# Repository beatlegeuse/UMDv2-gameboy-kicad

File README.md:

# UMDv2-gameboy-kicad
UMDv2 Gameboy Cartridge Adapter

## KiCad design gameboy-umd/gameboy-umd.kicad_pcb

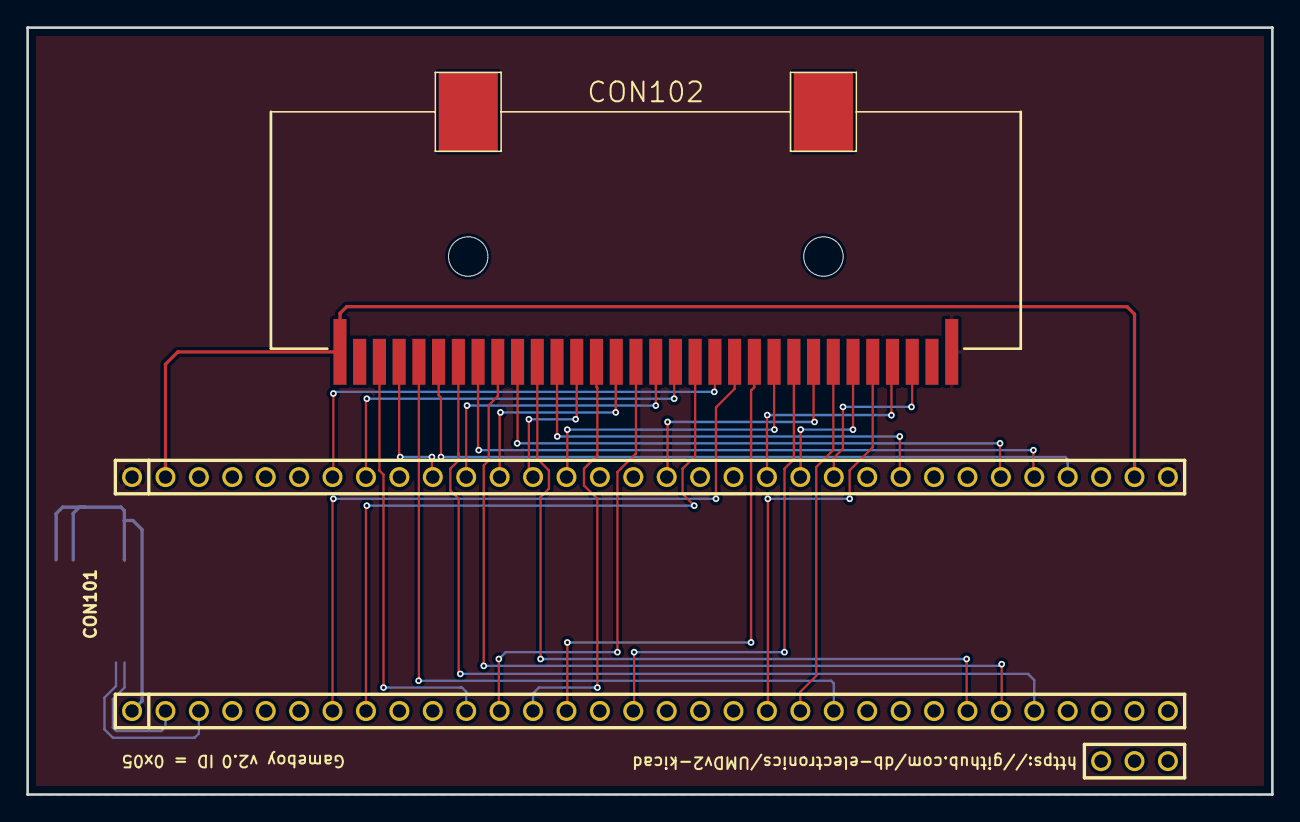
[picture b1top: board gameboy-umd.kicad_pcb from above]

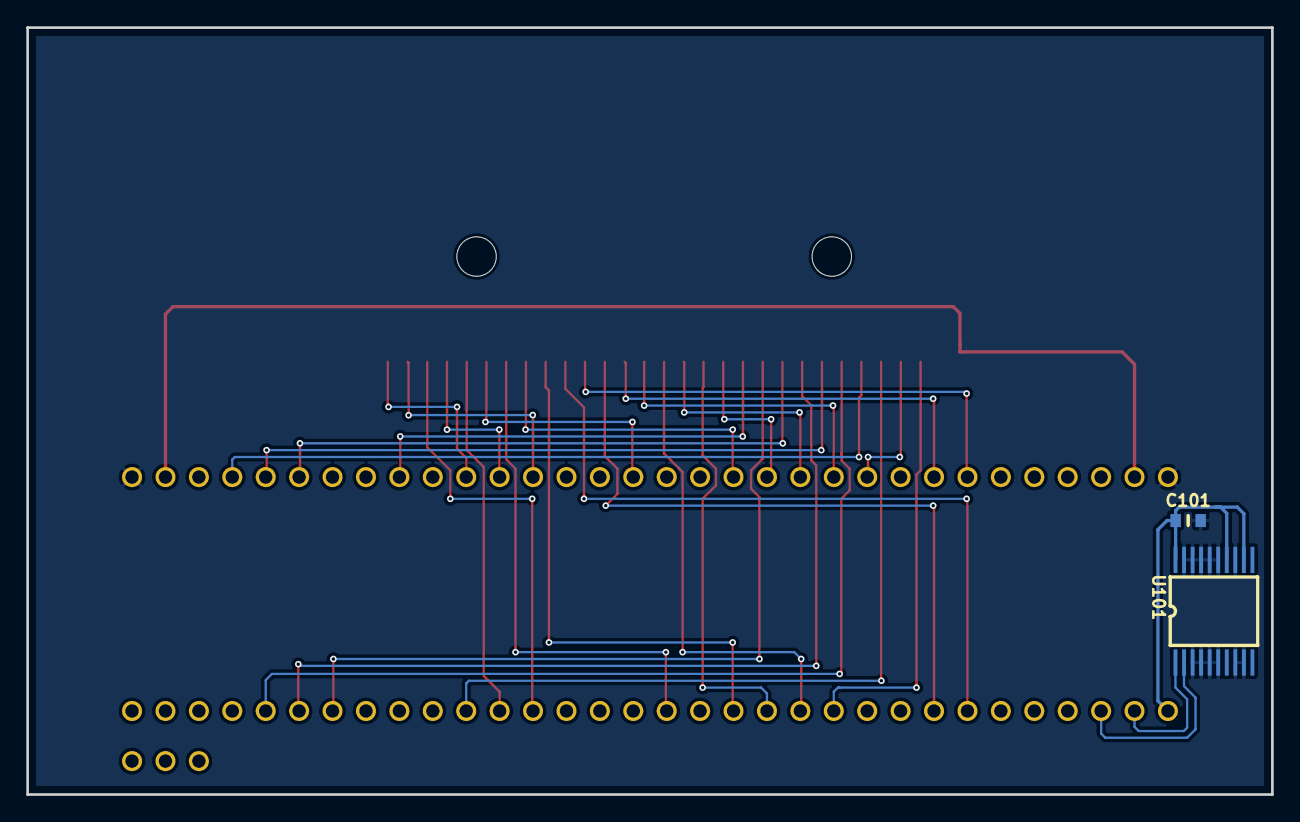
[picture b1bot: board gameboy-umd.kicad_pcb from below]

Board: 2 copper layers, 94.6 x 58.3 mm, 4 parts (2 on the bottom side), 33 nets.

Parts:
C101: 0.1uF/50V; 0603
CON101: UMDv2-CONN; UMD-CONN-DIP64
CON102: GB-CONN
U101: MCP23008T-E_SS; SSOP-20

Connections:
+3V3: C101.1, CON101.1, U101.12, U101.14, U101.20
/A0: CON101.36, CON102.6
/A1: CON101.28, CON102.7
/A2: CON101.37, CON102.8
/A3: CON101.27, CON102.9
/A4: CON101.38, CON102.10
/A5: CON101.26, CON102.11
/A6: CON101.41, CON102.12
/A7: CON101.52, CON102.13
/A8: CON101.13, CON102.14
/A9: CON101.53, CON102.15
/A10: CON101.12, CON102.16
/A11: CON101.54, CON102.17
/A12: CON101.57, CON102.18
/A13: CON101.8, CON102.19
/A14: CON101.58, CON102.20
/A15: CON101.7, CON102.21
/CS: CON101.22, CON102.5
/D0: CON101.14, CON102.22
/D1: CON101.51, CON102.23
/D2: CON101.16, CON102.24
/D3: CON101.48, CON102.25
/D4: CON101.21, CON102.26
/D5: CON101.44, CON102.27
/D6: CON101.20, CON102.28
/D7: CON101.45, CON102.29
/SCL: CON101.2, U101.1
/SDA: CON101.3, U101.2
/~RD: CON101.55, CON102.4
/~RESET: CON101.43, CON102.30
/~WR: CON101.11, CON102.3
GND: C101.2, CON101.33, CON101.64, CON102.32, U101.3, U101.4, U101.5, U101.6, U101.8, U101.9, U101.13, U101.15, U101.16, U101.17, U101.18, U101.19
Vcart: CON101.34, CON101.63, CON102.1

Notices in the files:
gameboy-umd/gameboy-umd.kicad_pcb:
Licensed Under CERN OHL v.1.2
